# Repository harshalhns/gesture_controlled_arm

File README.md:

IT IS A ROBOTIC ARM THAT REPLICATES HUMAN ARM MOVEMENT BY SENSING POSIITON.
THE POSITION OF ARM IS SENSED USING FLEX SENSORS.
THE ARM IS DRIVEN BY SERVO MOTORS.
THE ANAGLOG DATA COMING FROM FLEX SENSORS IS PROCESSED AND MOTORS WERE DRIVEN ACCORDINGLY.
IT IS DESIGNED ON THE AVR PLATFORM.

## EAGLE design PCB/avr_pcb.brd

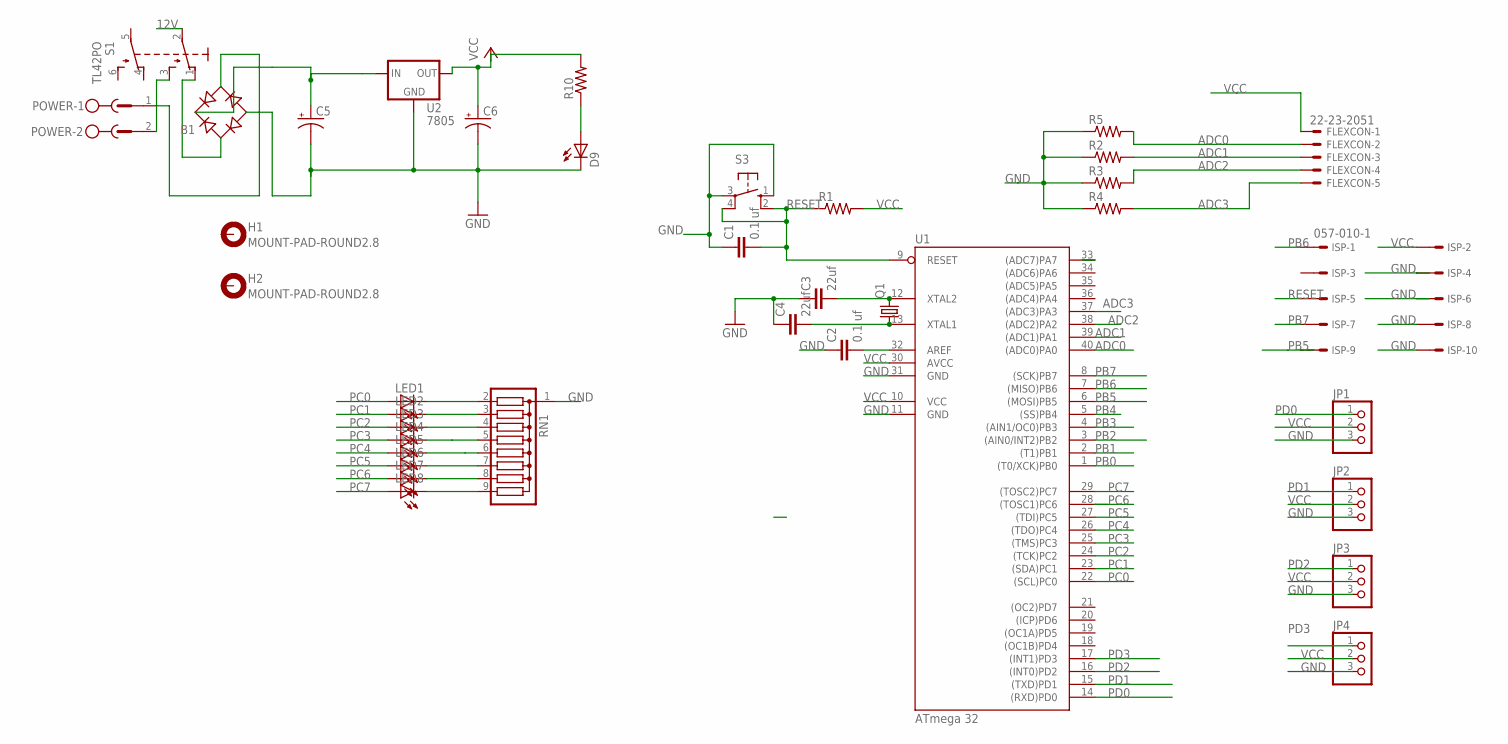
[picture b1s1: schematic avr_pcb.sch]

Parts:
B1: RB1A
C1, C2: 0.1 uf; C025-024X044
C3, C4: 22uf; C025-024X044
C5, C6: CPOL-USE5-6; E5-6
D9: LED3MM
FLEXCON: 22-23-2051
H1, H2: MOUNT-PAD-ROUND2.8; 2,8-PAD
ISP: 057-010-1
JP1, JP2, JP3, JP4: PINHD-1X3; 1X03
LED1, LED2, LED3, LED4, LED5, LED6, LED7, LED8: LED3MM
POWER: MSTBV2
Q1: CRYSTALHC18U-V; HC18U-V
R1, R2, R3, R4, R5, R10: R-US_0204/7; 0204/7
RN1: G08R; SIL9
S1: TL42PO; TL4XPO
S3: 10-XX; B3F-10XX
U1: ATmega 32; DIL40
U2: 7805; 78XXL

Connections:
12V: S1.2
ADC0: FLEXCON.2, R5.2, U1.40 ((ADC0)PA0)
ADC1: FLEXCON.3, R2.2, U1.39 ((ADC1)PA1)
ADC2: FLEXCON.4, R3.2, U1.38 ((ADC2)PA2)
ADC3: FLEXCON.5, R4.2, U1.37 ((ADC3)PA3)
GND: B1.-, C1.1, C2.1, C3.1, C4.1, C5.-, C6.-, D9.K (C), ISP.4, ISP.6, ISP.8, ISP.10, JP1.3, JP2.3, JP3.3, JP4.3, R2.1, R3.1, R4.1, R5.1, RN1.1, S3.1 (S), S3.3, U1.11 (GND), U1.31 (GND), U2.GND
unnamed: B1.AC1, S1.1 (O)
unnamed: D9.A, R10.1
unnamed: C3.2, Q1.2, U1.12 (XTAL2)
unnamed: C4.2, Q1.1, U1.13 (XTAL1)
unnamed: C2.2, U1.32 (AREF)
unnamed: B1.AC2, POWER.1
unnamed: LED1.K (C), RN1.2
unnamed: LED2.K (C), RN1.3
unnamed: LED3.K (C), RN1.4
unnamed: LED4.K (C), RN1.5
unnamed: LED5.K (C), RN1.6
unnamed: LED6.K (C), RN1.7
unnamed: LED7.K (C), RN1.8
unnamed: LED8.K (C), RN1.9
unnamed: POWER.2, S1.3 (S)
unnamed: B1.+, C5.+, U2.IN
PA7: U1.33 ((ADC7)PA7)
PB0: U1.1 ((T0/XCK)PB0)
PB1: U1.2 ((T1)PB1)
PB2: U1.3 ((AIN0/INT2)PB2)
PB3: U1.4 ((AIN1/OC0)PB3)
PB4: U1.5 ((SS)PB4)
PB5: ISP.9, U1.6 ((MOSI)PB5)
PB6: ISP.1, U1.7 ((MISO)PB6)
PB7: ISP.7, U1.8 ((SCK)PB7)
PC0: LED1.A, U1.22 ((SCL)PC0)
PC1: LED2.A, U1.23 ((SDA)PC1)
PC2: LED3.A, U1.24 ((TCK)PC2)
PC3: LED4.A, U1.25 ((TMS)PC3)
PC4: LED5.A, U1.26 ((TDO)PC4)
PC5: LED6.A, U1.27 ((TDI)PC5)
PC6: LED7.A, U1.28 ((TOSC1)PC6)
PC7: LED8.A, U1.29 ((TOSC2)PC7)
PD0: JP1.1, U1.14 ((RXD)PD0)
PD1: JP2.1, U1.15 ((TXD)PD1)
PD2: JP3.1, U1.16 ((INT0)PD2)
PD3: JP4.1, U1.17 ((INT1)PD3)
RESET: C1.2, ISP.5, R1.1, S3.2 (S1), S3.4 (P1), U1.9 (RESET)
VCC: C6.+, FLEXCON.1, ISP.2, JP1.2, JP2.2, JP3.2, JP4.2, R1.2, R10.2, U1.10 (VCC), U1.30 (AVCC), U2.OUT

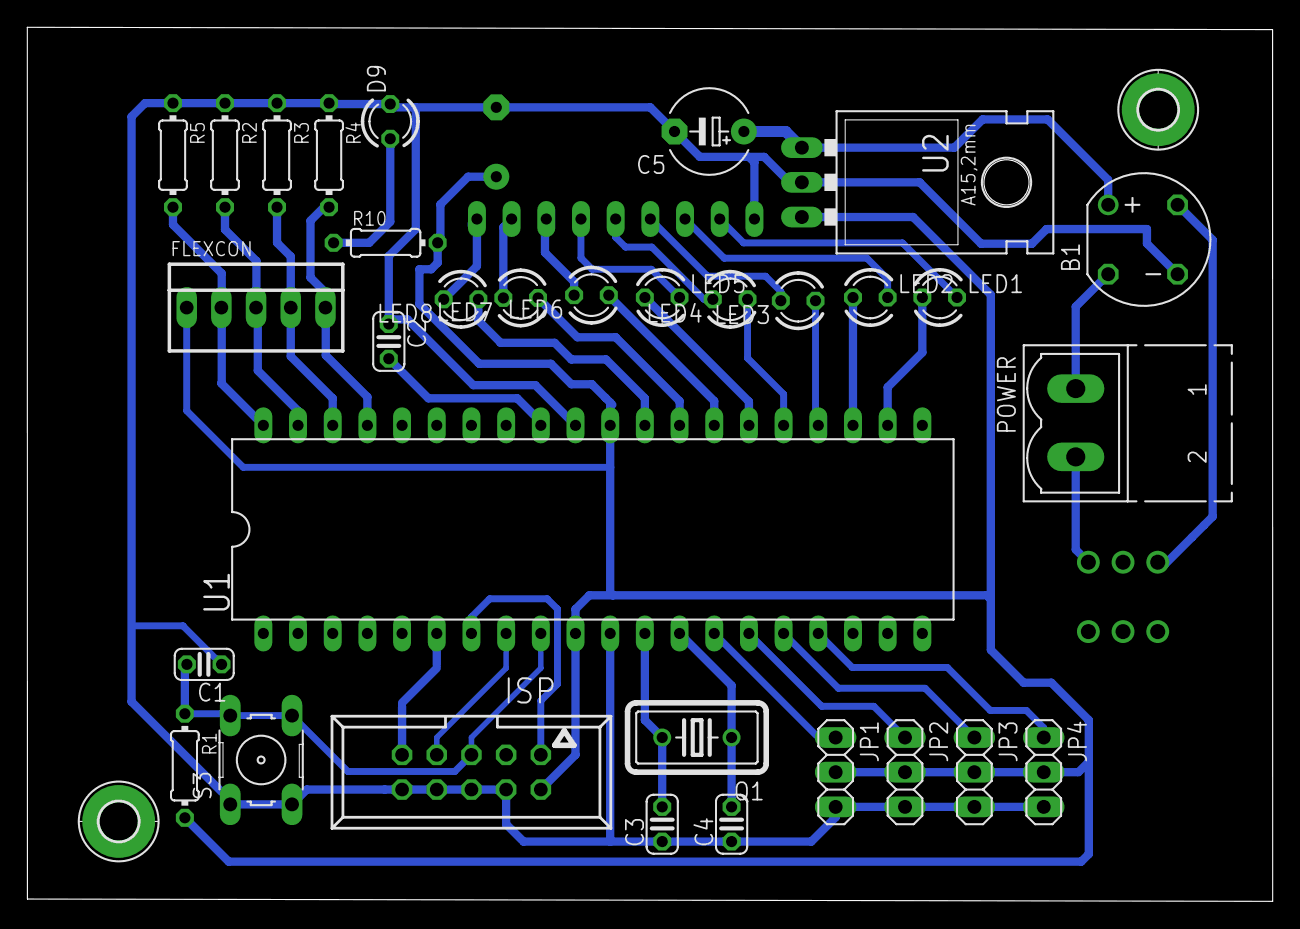
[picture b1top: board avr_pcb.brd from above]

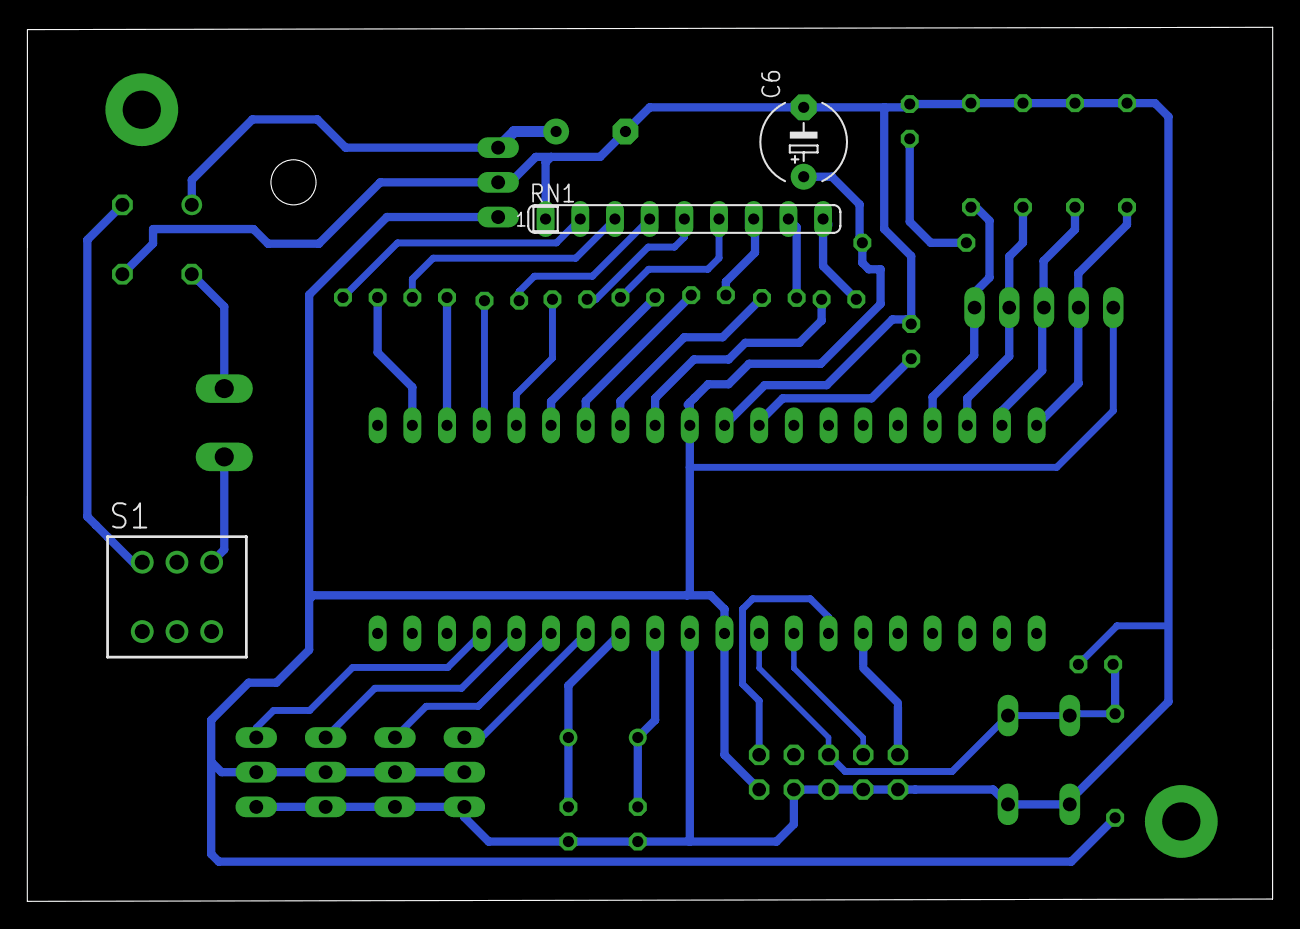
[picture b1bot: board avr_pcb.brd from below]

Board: 2 copper layers, 91.2 x 64.0 mm, 37 parts (3 on the bottom side), 38 nets.

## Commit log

2019-07-27 Create atmega32_code
2019-08-16 Create AA
